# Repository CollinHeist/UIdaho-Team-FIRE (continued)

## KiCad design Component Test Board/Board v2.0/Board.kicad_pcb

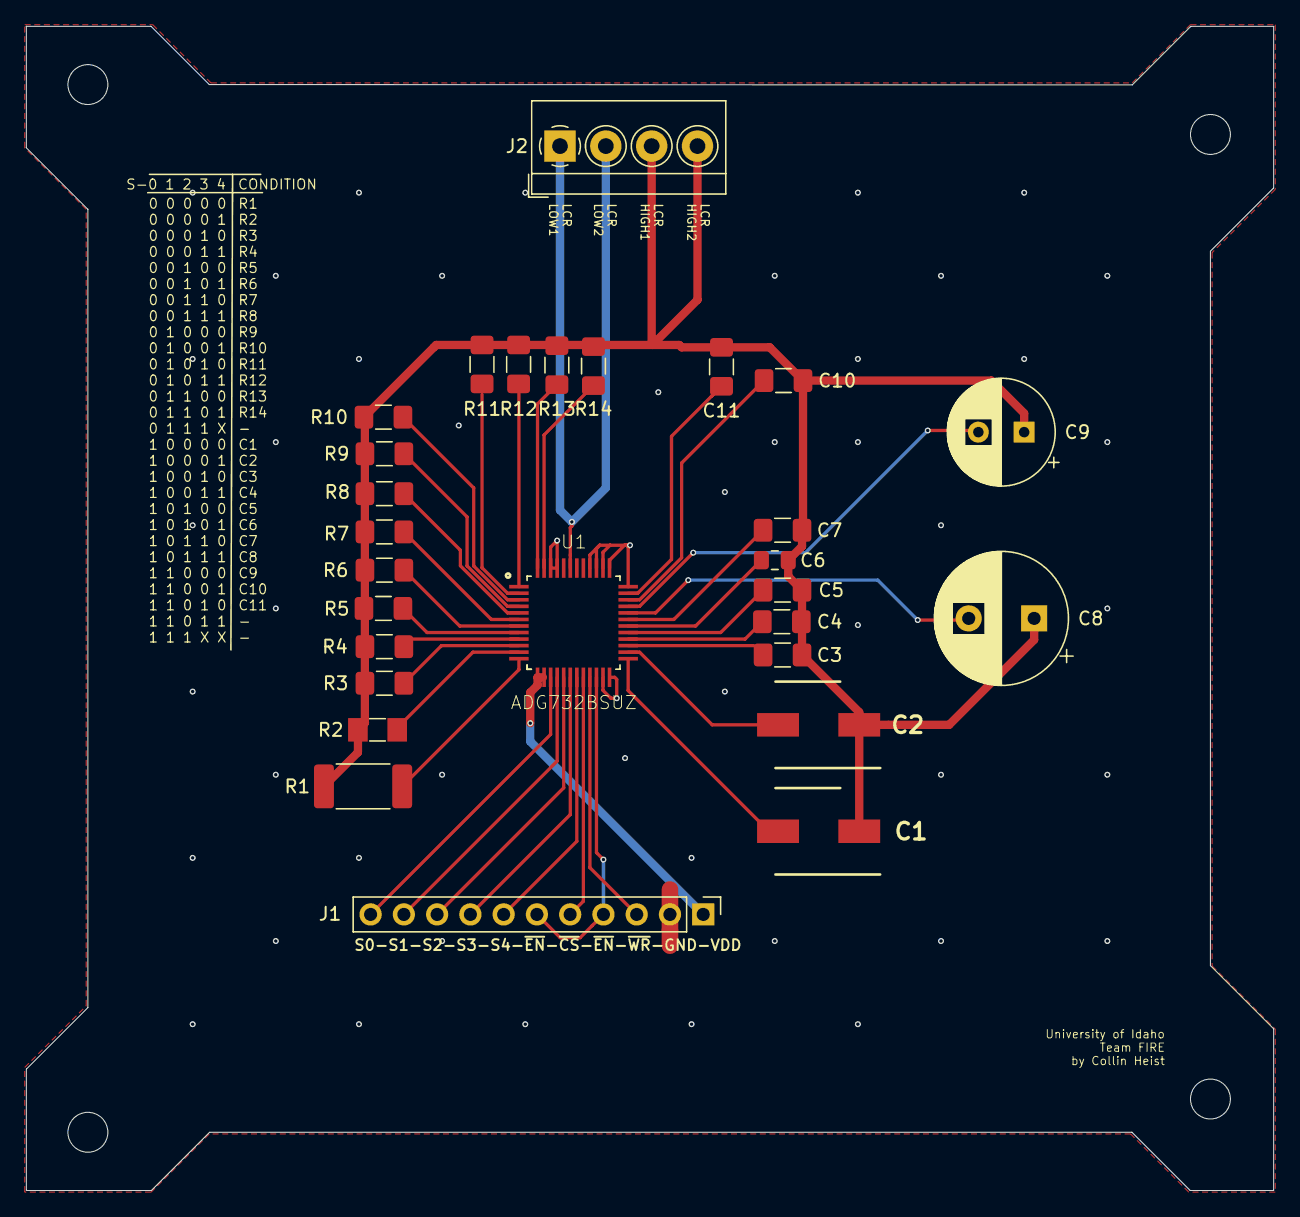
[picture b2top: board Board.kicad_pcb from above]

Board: 2 copper layers, 95.2 x 88.9 mm, 28 parts (0 on the bottom side), 37 nets.

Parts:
C1, C2: 47u; CAPAE660X640N
C3, C4, C5, C7: 0.1u; C_1206_3216Metric_Pad1.42x1.75mm_HandSolder
C6: 0.1u; C_0805_2012Metric_Pad1.15x1.40mm_HandSolder
C8: 10; CP_Radial_D10.0mm_P5.00mm
C9: 2.2; CP_Radial_D8.0mm_P3.50mm
C10, C11: 47u; C_1206_3216Metric_Pad1.42x1.75mm_HandSolder
J1: Conn_01x11; PinHeader_1x11_P2.54mm_Vertical
J2: Screw_Terminal_01x04; TerminalBlock_4Ucon_1x04_P3.50mm_Horizontal
R1: 1.5k; R_2512_6332Metric_Pad1.52x3.35mm_HandSolder
R2: 1k; R_MiniMELF_MMA-0204
R3, R4, R5: 1k; R_1206_3216Metric_Pad1.42x1.75mm_HandSolder
R6: 20m; R_1206_3216Metric_Pad1.42x1.75mm_HandSolder
R7: 470m; R_1206_3216Metric_Pad1.42x1.75mm_HandSolder
R8: 100; R_1206_3216Metric_Pad1.42x1.75mm_HandSolder
R9, R10, R11, R12, R13, R14: 10k; R_1206_3216Metric_Pad1.42x1.75mm_HandSolder
U1: ADG732BSUZ; QFP50P900X900X120-49N

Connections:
GND: J1.2, U1.23, U1.24, U1.36, U1.37, U1.38, U1.39, U1.40, U1.45, U1.46
LCR_HIGH1: C1.1, C2.1, C3.1, C4.1, C5.1, C6.1, C7.1, C8.1, C9.1, C10.1, C11.1, J2.3, J2.4, R1.2, R2.2, R3.2, R4.2, R5.2, R6.2, R7.2, R8.2, R9.2, R10.2, R11.2, R12.2, R13.2, R14.2
LCR_LOW1: J2.1, J2.2, U1.43
unnamed: C1.2, U1.25
unnamed: C2.2, U1.26
unnamed: C3.2, U1.27
unnamed: C4.2, U1.28
unnamed: C5.2, U1.29
unnamed: C6.2, U1.30
unnamed: C7.2, U1.31
unnamed: C8.2, U1.32
unnamed: C9.2, U1.33
unnamed: C10.2, U1.34
unnamed: C11.2, U1.35
unnamed: R1.1, U1.12
unnamed: R2.1, U1.11
unnamed: R3.1, U1.10
unnamed: R4.1, U1.9
unnamed: R5.1, U1.8
unnamed: R6.1, U1.7
unnamed: R7.1, U1.6
unnamed: R8.1, U1.5
unnamed: R9.1, U1.4
unnamed: R10.1, U1.3
unnamed: R11.1, U1.2
unnamed: R12.1, U1.1
unnamed: R13.1, U1.48
unnamed: R14.1, U1.47
SELECT0: J1.11, U1.15
SELECT1: J1.10, U1.16
SELECT2: J1.9, U1.17
SELECT3: J1.8, U1.18
SELECT4: J1.7, U1.19
VDD: J1.1, U1.13, U1.14
~CS: J1.5, U1.20
~EN: J1.4, J1.6, U1.22
~WR: J1.3, U1.21

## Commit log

2020-04-28 Fix: connection of IO-RI
2020-04-28 Starting complete BOM generation
    - Finished schematic(s)
    - Started BOM information assignment for final BOM sent to NASA
2020-04-29 Fixed libraries, added BOM info to most components
    - Fixed MCP1826T library to be a part of Team-Fire library (not separate)
    - Deleted useless library files for various pieces (such as ImportGuides, etc.)
    - Fixed inductor value specification for boost converter
2020-04-29 Added EEE-FK1H390SV
    - Created EEE-FK1H390SV symbol and footprint
    - Added EEE-FK1H390SV to Team-FIRE libraries
    - Added EEE-FK1H390SV to 8 to 30V boost circuit
2020-04-29 Finished component selection for Bus Translators
    - Finished filling out all details for every component in Bus Translator block
    - Annotated existing schematic
2020-04-30 Made a lot of changes...
    - Added symbol, footprint for Micro USB B connector
    - Fixed Flash Memory schematic
    - Added details for many components
2020-04-30 fixed issue
2020-04-30 Fixed some stuff (woops)
2020-04-30 Fixed alignment(s), added component details
2020-04-30 Labelled finished sections on schematic, picked LEDs
    - Labelled all finished schematic sections if they've been part-selected / verified (and by whom)
    - Selected the four debug LEDs and filled out BOM info
    - Filled out info for Power/TES connectors
    - Filled out info for RF connector
    - Filled out info for 5 to 3.3V regulator
    - Filled out info for 8 to 5V switching regulator
2020-05-01 Selected components for SAMD51
    - Selected components for crystal oscillators
    - Selected component for reset button
    - Selected component for flash memory (cant find details for flash module...)
    - Ran schematic annotation
2020-05-01 30V net for boost
2020-05-01 annotated stuffff
2020-05-01 Fix positioning of SAMD51
2020-05-01 Fix: issues with merge
2020-05-05 Minor changes..
2020-05-06 Finished SAMD part selection, fixed alignment on all sheets
    - Fixed part selection for all SAMD51 sheet components
    - Fixed grid misalignment in SAMD51 components
    - Had to remove all SAMD51 additional text for this fix
    - Added no connects to unused pins for SAMD51
    - Removed component selection comments for all pages
    - Add components selected except one or two boost circuit components and the SIM card connector.
2020-05-06 minor aesthetic change
2020-05-06 Added footprints (& potential one for SIM)
2020-05-06 Fixed some library problems
    - Deleted uselss import files
    - Fixed B26013F library files
    - Fixed IHLP6767GZER220M11 library files
    - Fixed weird library reference for inductor, transistor, and diode
    - Imported shelby's files to the Team-FIRE library
2020-05-06 Finished schematic
    - Added 47338-2001 symbol, footprint, and model to schematic
    - Added 47338-2001 to Team-FIRE library
    - Created custom SIM card holder symbol
    - Added all component description values for SIM card holder
2020-05-06 Deleted EAGLE Managed Libraries, removed .net from .gitignore
    - Deleted old EAGLE Managed libraries, given we aren't using them we can just remove them
    - Deleted .net (for netlist files) entry from .gitignore so we can share netlist exports
2020-05-06 Replaced transistor symbol, and footprint
    - Had to replace the CSD18543Q3AT transistor with a custom symbol, footprint and 3D model to account for the 9-pin package it resides in (not a 3 pin as the symbol depicts)
2020-05-06 Fixed flash memory symbol assignment, generated final netlist
    - Symbol for Flash unit was a reference to a DSSOP package, and thus had the wrong pin names for that footprint; updated the symbol to reflect the correct footprint
    - Generated new netlist based on complete schematic, added all symbols to the PCB file
2020-05-06 Did some preliminary PCB work
    - Started the PCB layout
    - Put connectors in their probable spots
2020-05-07 Finished PCB
    - Added various 3D models for a complete 3D visualization of the PCB
    - Generated a finalized netlist
    - Fixed misnamed net from IR_SIM_RST to IR_SIM_RESET
    - Finished all component placement for the PCB; the only work remaining are the mounting holes, and the grounding vias for the IRIDIUM
2020-05-07 Minor changes
    - Made some little changes; not really important.
2020-05-07 Moved stuff
2020-05-07 Increased trace width for boost circuitry & added silk screen
2020-05-10 Deleted unused LED's, finished mounting for IRIDIUM
    - Delete the two unused LEDs from schematic and layout
    - Added grounding vias for antenna connection
    - Added grounding vias for IRIDIUM 9523 modem
    - Added keepout zones (except GND) for antenna and modem
2020-05-27 Moved some stuff
